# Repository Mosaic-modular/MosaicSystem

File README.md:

<h1 align="center">
    
    <br />
    Mosaic system design guidelines
  </a>
  
</h1>

<div align="center">
  <br />
    
  <br />
</div>

---

## About

Design files for use with the open source Mosaic system. All the footprints are verified and fully tested.
For more info, please visit <a href="https://mosaicsynth.com/index.php/system-info/">Mosaicsynth.com</a>

## Getting Started
Copy the content of the templates folder to the user templates folder:

    Unix: ~/kicad/template/

    Windows: C:\Documents and Settings\username\My Documents\kicad\template or C:\Users\username\Documents\kicad\template

    Mac: ~/Documents/kicad/template/

Go to <b> File → New Project → New Project from Template </b> and select the template you want from the user templates tab.

The templates come with all of the design rules and settings needed to design your mosaic system modules and have them manufactured by JLCPCB. If you use another manufacturer please make sure to check the design rules. 

All of the symbols have the preferred footprint already assigned so you can just duplicate the ones you need and after you have finished your design delete all the unwanted parts. 

## Workflow

1. In kicad file -> new project from template -> user templates and select the one you need. (See getting started on how use the custom templates in kicad)
2. Start with the schematic and design your circuit. I have included some commonly used symbols so you can just copy and paste them to get started. It is good practice to make your schematic clean and easy to read. A few tips:
   - Always make sure you have at least a 2 space wire between components. This avoids having to connect components directly and makes it easier to move things around later.
   - Avoid points where 4 wires connect. This can be confusing when it's not quite clear wich wires connect to wich.
   - Only use right angle wires and space your symbols enough to make it easily readable.
   - Ground symbols always point down and power symbols always point up. (negative voltages like -12V are the exception and they point down)
   - Use standard symbols as much as possible, this helps with compatability. There are only a few Mosaic specific symbols like the input, output and power connector.
3. After your design is done you can delete any of the unused spare symbols and decide on the options on the lower part of the schematic template. You can include the logo and some JLCPCB specific parts like a production number placeholder or tooling holes for automated assembly.
4. When your schematic is fully done, triple check everything and move on to assigning footprints.
5. Create a PCB from the schematic and place the components off to the side for now. The template comes with the standard design rules for the JLCPCB 2 layer boards and some common trace widths and via sizes.
6. Start by placing your inputs,outputs, controls and power connector. I like to use a course grid of 2.5mm for this. The spacing between banana sockets should be at least 10mm, leaving you room for 4 sockets in the 50mm size.
7. Place the rest of your components on the bottom. I use 0805 and SOIC packages for some simpler modules but when you have a lot of components you can choose to go to 0402 and have your boards assembled. I generally find that with good component placement and some planning most designs will fit in the space between the bigger components. PCB design is kind of a dark art and there are so many ways to approach it so do your own research and look at lots of examples.
8. The groundfill on the top and bottom is always connected with vias around the mounting holes but it never hurts to add some extra vias to make sure both groundplanes are connected in several spots.
9. When you're done with placing and routing all the components on the bottom you can focus on the graphics on the frontpanel. You have 4 colours at your disposal, soldermask(generally black), silkscreen(generally white), uncovered surface finish(generally silver) and the bare FR4 board. I recommend keeping the graphics quite bold to make it readable.
10. Don't forget the scale that you're working on, a 50x50 module can get cramped quite quickly. Make sure you have enough space to use all the different functions and still be able to read any text or graphics. Going to a 50x100 or 100x100 is always an option.
11. Check footprints, component availability, routing, clearance and silkscreen legend. Repeat. Repeat. This part of designing a module requires a lot of back and forth and it's so easy to miss something. I always recommend to leave it for a day and check everything again.
12. Solder, assemble, make incredible music.
13. Share your project and let other know what you've made.

## Support
<a href = "https://mosaicsynth.com/index.php/contact/"> contact form </a>

## Authors & contributors

Original files and system designed by [Mosaic modular synthesizers](https://github.com/Mosaic-modular).

## License

This project is licensed under the <a href="https://ohwr.org/cern_ohl_w_v2.pdf">CERN OHL v2 W</a> license. 

See [LICENSE](LICENSE) for more information.

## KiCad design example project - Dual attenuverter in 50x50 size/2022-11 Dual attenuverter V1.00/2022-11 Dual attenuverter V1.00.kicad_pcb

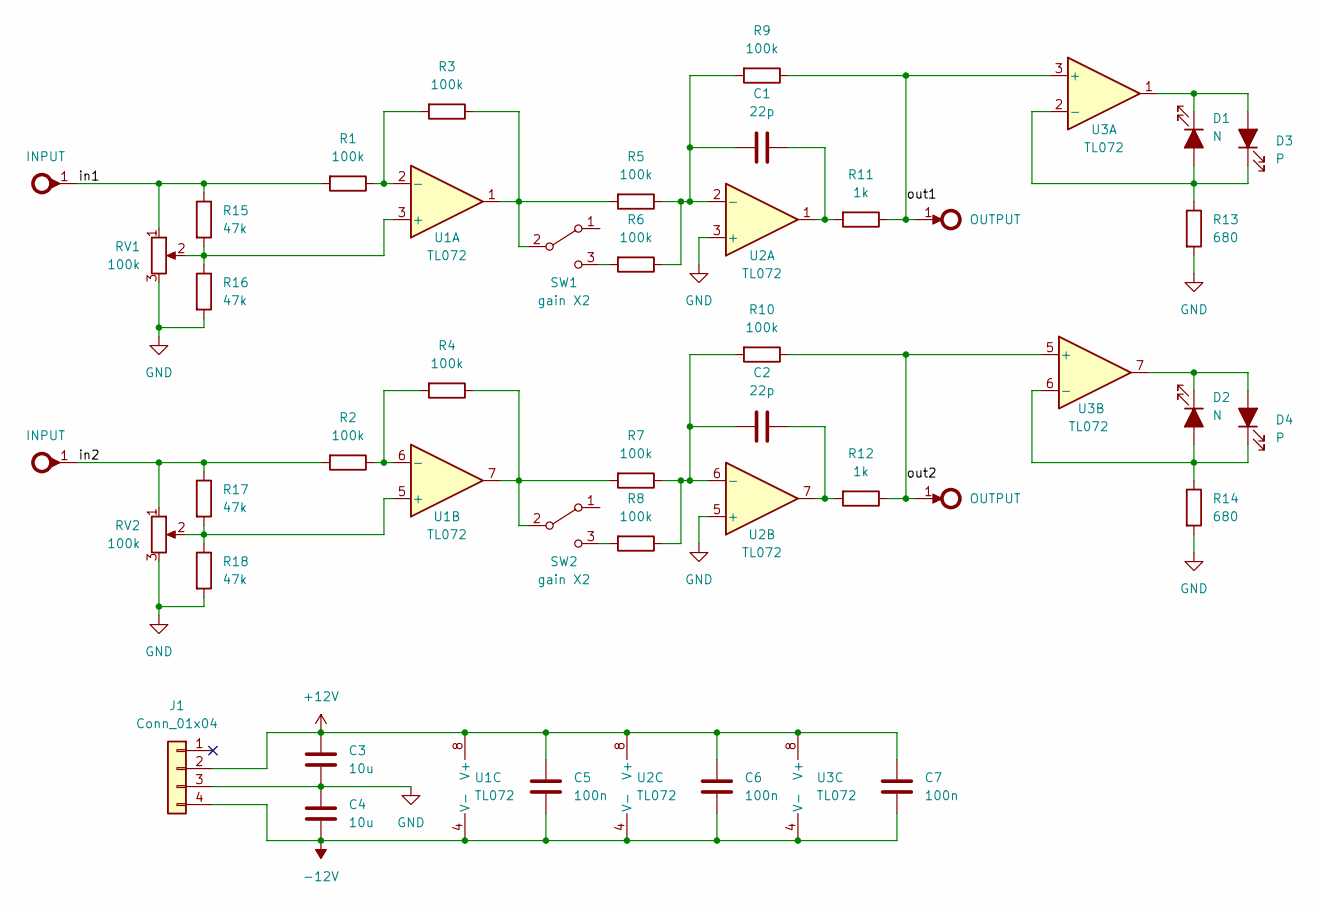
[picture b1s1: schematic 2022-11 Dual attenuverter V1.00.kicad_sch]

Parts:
C1, C2: 22p; C_0805_2012Metric
C3, C4: 10u; C_0805_2012Metric
C5, C6, C7: 100n; C_0805_2012Metric
D1, D2: N; LED 0805 reverse mount
D3, D4: P; LED 0805 reverse mount
J1: Conn_01x04; JST_B4B-PH-SM4-TB_LF_SN_0
J2, J3: INPUT; BANANA_4mm_non_insulated_banana_jack
J4, J5: OUTPUT; BANANA_4mm_non_insulated_banana_jack
R1, R2, R3, R4, R5, R6, R7, R8, R9, R10: 100k; R_0805_2012Metric
R11, R12: 1k; R_0805_2012Metric
R13, R14: 680; R_0805_2012Metric
R15, R16, R17, R18: 47k; R_0805_2012Metric
RV1, RV2: 100k; RV16AF-20-17K
SW1, SW2: gain X2; SS-12D10
U1, U2, U3: TL072; SOIC-8_3.9x4.9mm_P1.27mm

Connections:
+12V: C3.2, C5.2, C6.2, C7.2, J1.2, U1.8 (V+), U2.8 (V+), U3.8 (V+)
-12V: C4.1, C5.1, C6.1, C7.1, J1.4, U1.4 (V-), U2.4 (V-), U3.4 (V-)
/in1: J2.1, R1.2, R15.1, RV1.1
/in2: J3.1, R2.2, R17.1, RV2.1
/out1: J4.1, R9.1, R11.1, U3.3 (+)
/out2: J5.1, R10.1, R12.1, U3.5 (+)
GND: C3.1, C4.2, J1.3, R13.2, R14.2, R16.2, R18.2, RV1.3, RV2.3, U2.3 (+), U2.5 (+)
unnamed: C1.1, R5.1, R6.1, R9.2, U2.2 (-)
unnamed: C1.2, R11.2, U2.1
unnamed: C2.1, R7.1, R8.1, R10.2, U2.6 (-)
unnamed: C2.2, R12.2, U2.7
unnamed: D1.1 (K), D3.2 (A), U3.1
unnamed: D1.2 (A), D3.1 (K), R13.1, U3.2 (-)
unnamed: D2.1 (K), D4.2 (A), U3.7
unnamed: D2.2 (A), D4.1 (K), R14.1, U3.6 (-)
unnamed: R1.1, R3.2, U1.2 (-)
unnamed: R2.1, R4.2, U1.6 (-)
unnamed: R3.1, R5.2, SW1.2 (B), U1.1
unnamed: R4.1, R7.2, SW2.2 (B), U1.7
unnamed: R6.2, SW1.3 (C)
unnamed: R8.2, SW2.3 (C)
unnamed: R15.2, R16.1, RV1.2, U1.3 (+)
unnamed: R17.2, R18.1, RV2.2, U1.5 (+)

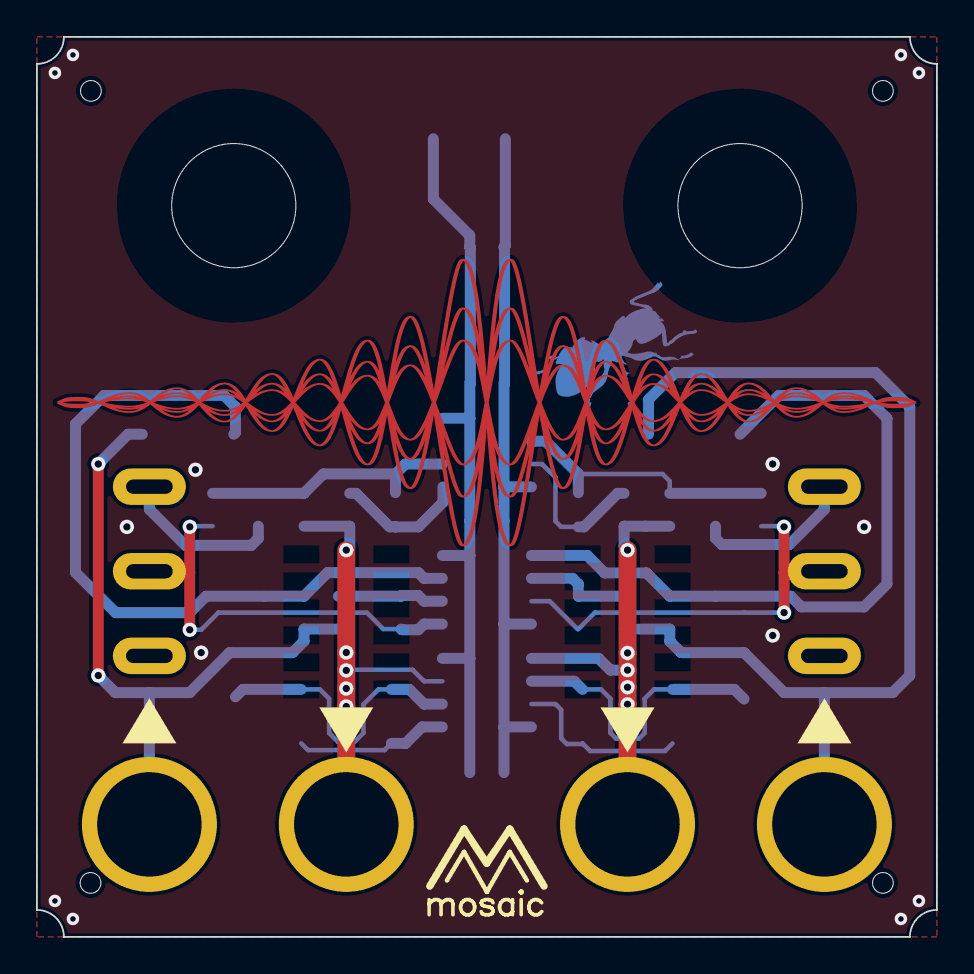
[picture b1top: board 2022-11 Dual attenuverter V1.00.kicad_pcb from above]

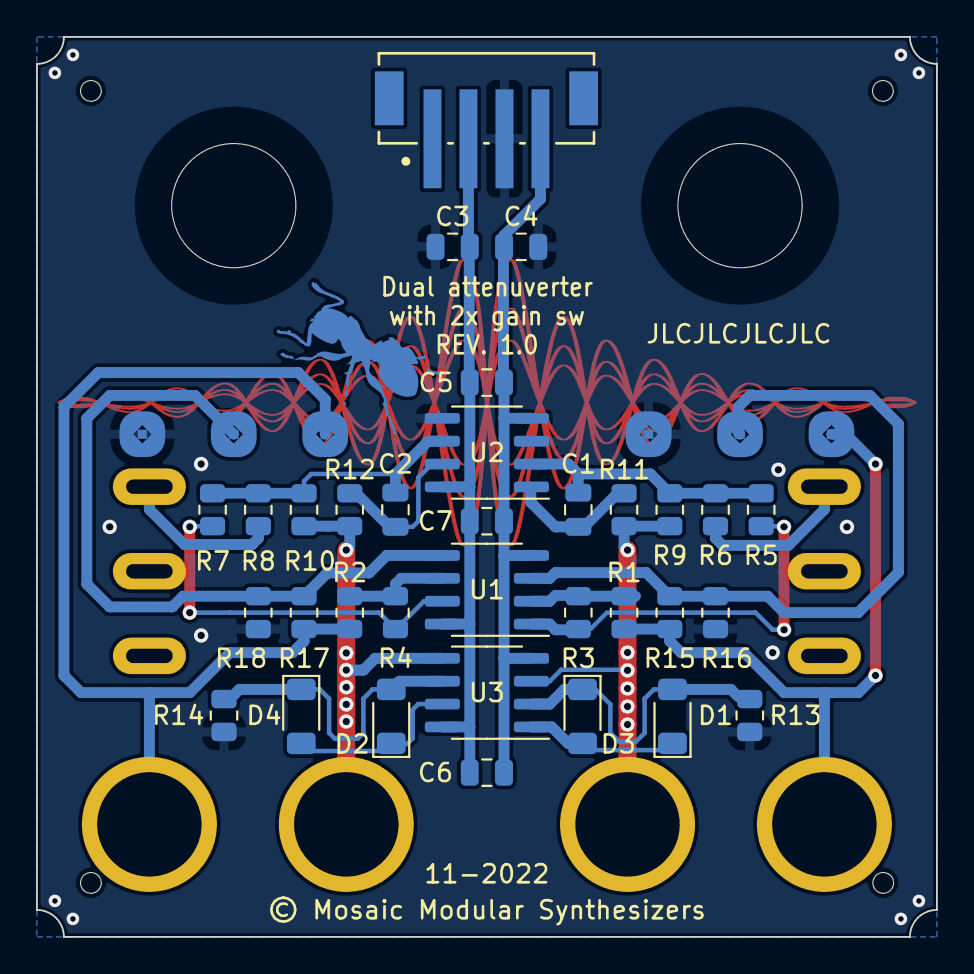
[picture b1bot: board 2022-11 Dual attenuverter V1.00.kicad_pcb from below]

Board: 2 copper layers, 50.0 x 50.0 mm, 42 parts (29 on the bottom side), 23 nets.

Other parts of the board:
RefV: Val**; MM_LOGO

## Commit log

2022-12-07 initial
2022-12-13 V1.00
2022-12-13 Update LICENSE
2023-08-07 V1.1
    Clean up of some redundant footprints and added the correct polygons for the keepout area of the corners.
2023-08-07 added example
2023-08-18 update templates
    Updated templates now have the current polygons for the soldermask keepout area and restrict any traces or components from entering those areas
2024-03-31 V2
    New version for use with special standoffs for locating.

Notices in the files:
example project - Dual attenuverter in 50x50 size/2022-11 Dual attenuverter V1.00/2022-11 Dual attenuverter V1.00.kicad_pcb:
© Mosaic Modular Synthesizers
